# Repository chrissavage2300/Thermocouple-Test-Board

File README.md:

# Thermocouple-Test-Board
Uses both the MCP9801 and MCP3425 onboard temperature sensor and 16 bit ADC to read a thermocouple

* Parts list is self explanatory. MCP9801 temp sensor and MCP3425 SOT ADC. The 16bit or 18 bit versions should work. 

* C3 and C4 are 4.7uF to 10uF

* C1 and C2 are 0.1uF or lesser to help filter out the input.

* JP1 is a standard 2.54mm screw terminal block. J2 is 2.54mm pins.

* R1 and R2 are 4.7k ohm resistors.

  ## The Code

Rather than using a dedicated Thermocouple IC to read a thermocouple, we can just use a sensitive ADC to read it. K type thermocouples have a signal of 40uV/C, which is pretty small. So we have to amplify it using a PGA. We also need a high resolution ADC. Ive found that 16 to 18 bits should give enough resolution and I only need it to be within 1 degree C or better. The algorithm works by first setting the PGA to 4x, then using the full 16 bits of the ADC. We then use some floating point math to get our voltage of the thermocouple. 

After that, we convert the temperature reading of the MCP9801 to a voltage. We dont add the temperatures together, rather, we add the voltages. Once the two voltages are added, then we shove it into the thermocouple formula to get our temperature. 

In testing Ive found it to be within +/-1C°. I could max out the PGA and use 8x mode, but 4x gives me roughly 1.5 codes per degree C. I tested this circuit both at boiling water (as close as I can get it) and freezing water. Freezing water is easy, I used an insulated bottle and tried to crush up ice as best as I can. Boiling water is a bit different as I had to move my kettle into the same room, and it doesnt stay boiling either, so measurements had to be quick. 

This code is currently being tested on a dspic33. Anything that has I2C will work, as long as you have a library to do so. 

## Math

Some of this was taken from the datasheet of a similar ADC. We are basically using a 16 bit ADC, set for max resolution. I initially had selected a PGA of 8 but decided that I dont need that much accuracy.
If you need that much accuracy, you can re-do the math to figure out your code value. Based on these formula's above, for the temperature I will be using, my max code that I will recieve is 640 (base 10). 

Once you follow the main formula, you are now reading voltage and can use it how ever you would like. For this application, the final result is in uV * 100, ie a voltage of 40uV will be read as 400. Next the cold temperature from the MCP9800 needs to be converted into a voltage. I used a linearized formula for that, that I found using Libre Office. The truncated  formula is basically "Temperature*4" so we use integers only. The exact formula is:

Note that I multiply by 0.01. This is so we dont have to divide by 100.

Then we perform an addition on the two values:

Now we can finally use this voltage in the polynomial formula given by NIST to figure out our temp. In my case though, I used a linearized formula, since K thermocouples are mostly linear. I also used a short version due to using integers:

This is the exact linearized formula. Its within a degree or two.

This is the integer formula I used to do most of the math. In testing, its also accurate to within a degree or two, which is fine. My final system can only change that much. As far as the code goes, you now have your final temp, however, I did perform a division by 10000 after this because the number is too big to be used. 

## Schematic

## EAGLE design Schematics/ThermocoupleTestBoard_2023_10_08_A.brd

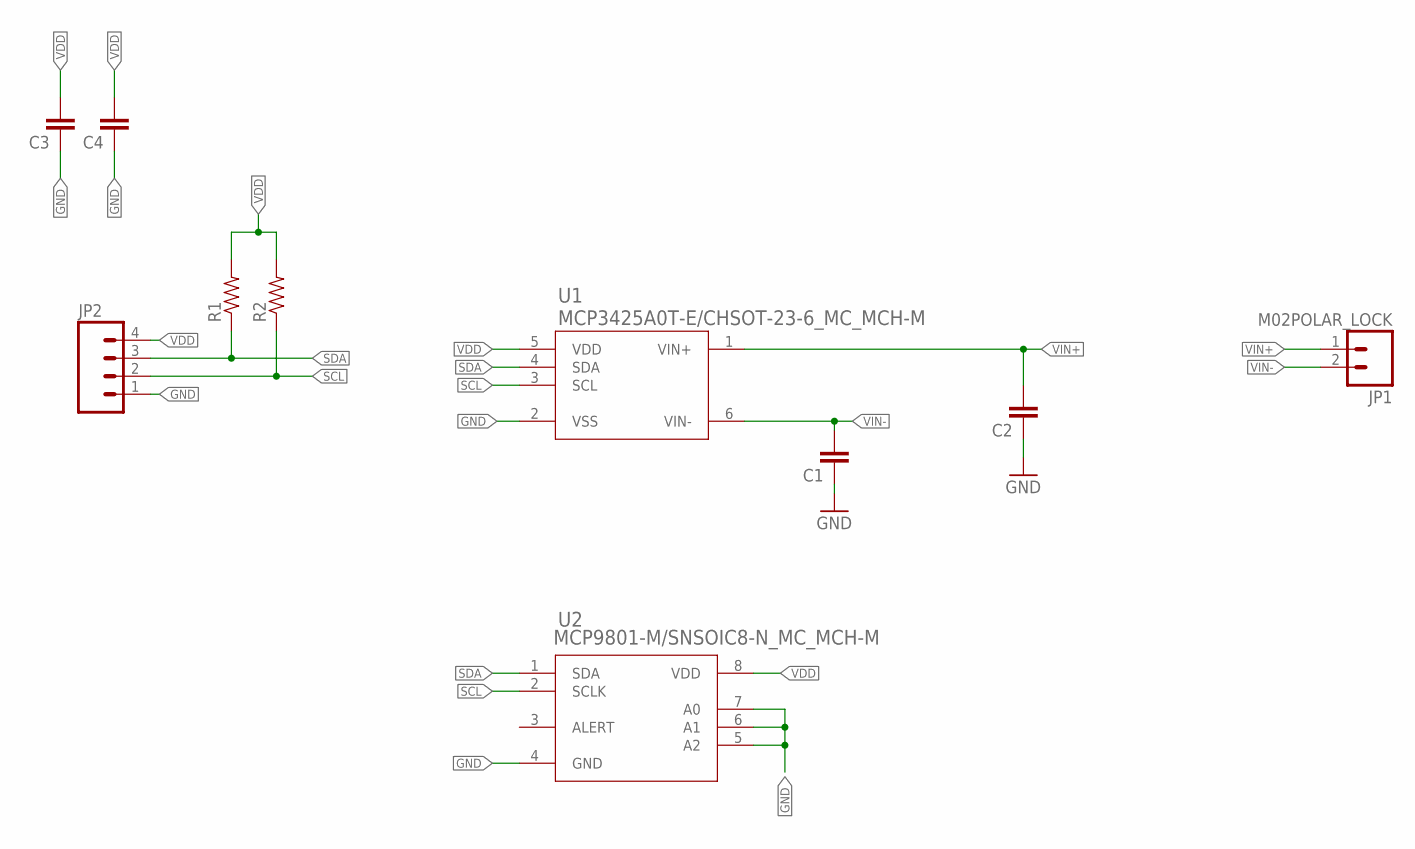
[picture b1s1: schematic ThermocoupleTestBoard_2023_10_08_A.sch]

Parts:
C1, C2, C3, C4: CAP1206; 1206
JP1: M02POLAR_LOCK; MOLEX-1X2_LOCK
JP2: M04LOCK; 1X04_LOCK
R1, R2: RESISTOR1206; 1206
U1: MCP3425A0T-E/CHSOT-23-6_MC_MCH-M; SOT-23-6_MC_MCH-M
U2: MCP9801-M/SNSOIC8-N_MC_MCH-M; SOIC8-N_MC_MCH-M

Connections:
GND: C1.1, C2.1, C3.1, C4.1, JP2.1, U1.2 (VSS), U2.4 (GND), U2.5 (A2), U2.6 (A1), U2.7 (A0)
SCL: JP2.2, R2.1, U1.3 (SCL), U2.2 (SCLK)
SDA: JP2.3, R1.1, U1.4 (SDA), U2.1 (SDA)
VDD: C3.2, C4.2, JP2.4, R1.2, R2.2, U1.5 (VDD), U2.8 (VDD)
VIN+: C2.2, JP1.1, U1.1 (VIN+)
VIN-: C1.2, JP1.2, U1.6 (VIN-)

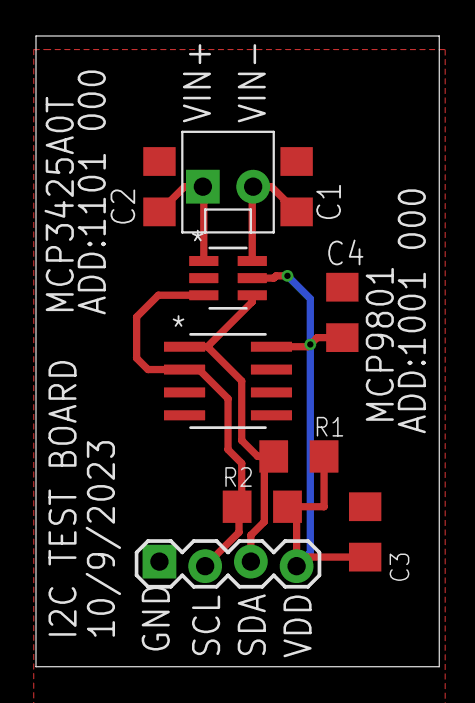
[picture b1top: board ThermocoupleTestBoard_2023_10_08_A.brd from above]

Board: 2 copper layers, 22.4 x 35.0 mm, 10 parts (0 on the bottom side), 6 nets.

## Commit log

2024-07-07 Rename readme.me to readme.md

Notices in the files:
parts and their libraries:
SparkFun-Capacitors: Licensing: Creative Commons ShareAlike 4.0 International - https://creativecommons.org/licenses/by-sa/4.0
COPYRIGHT: Copyright (C) 2023 Ultra Librarian. All rights reserved.
